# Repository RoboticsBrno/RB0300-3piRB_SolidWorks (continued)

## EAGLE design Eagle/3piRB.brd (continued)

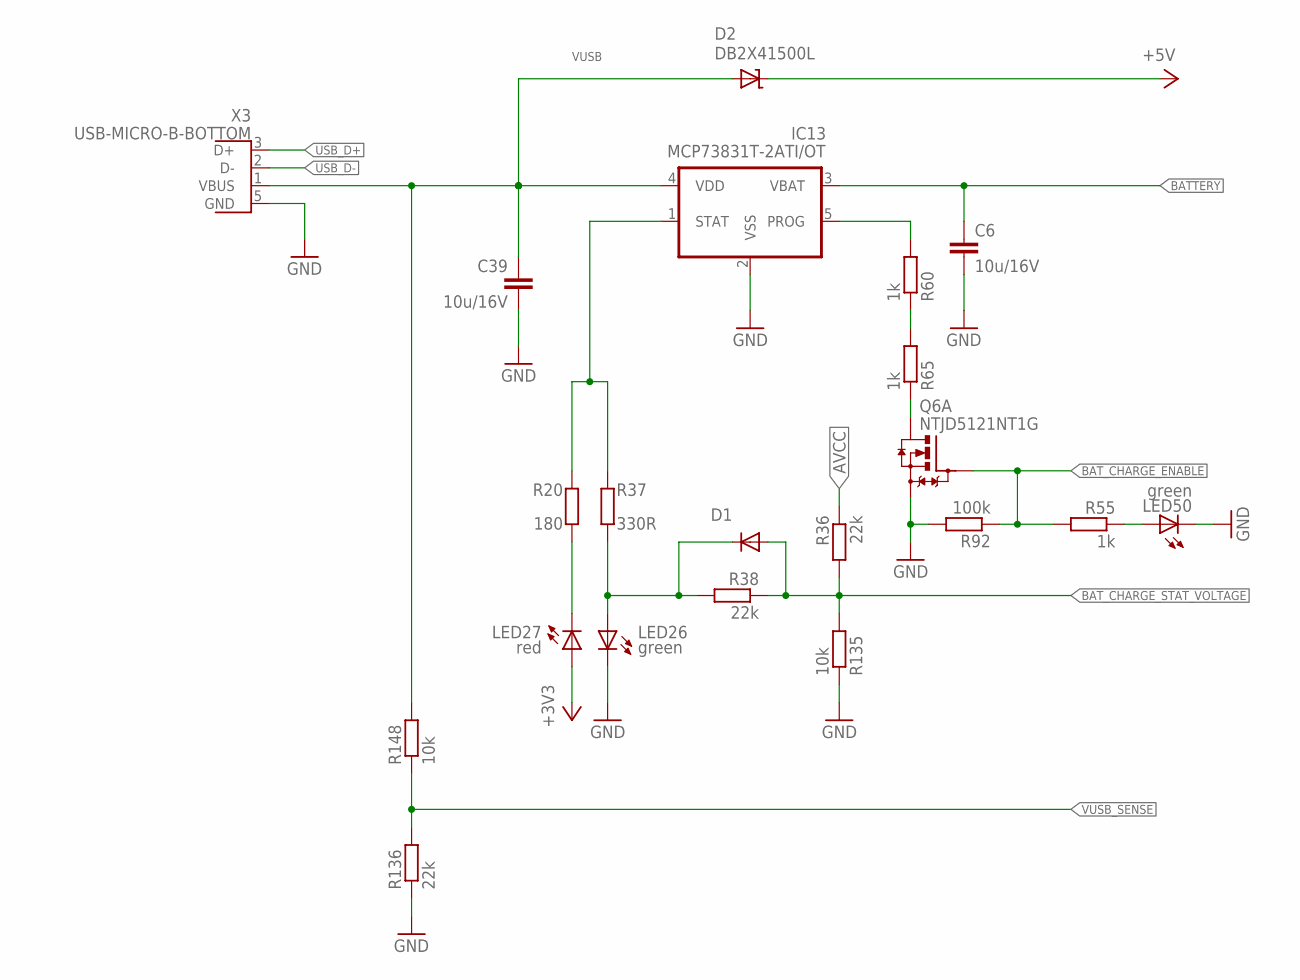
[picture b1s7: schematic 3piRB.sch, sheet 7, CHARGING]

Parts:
C6, C39: 10u/16V; C0805
D1: DIODE-0603; D0603
D2: DB2X41500L; SOD123
IC13: MCP73831T-2ATI/OT; SOT95P300X145-5N
LED26, LED50: green; CHIPLED_0603
LED27: red; CHIPLED_0603
Q6: NTJD5121NT1G; SOT363
R20: 180; _0402MP
R36, R38, R136: 22k; _0402MP
R37: 330R; _0402MP
R55, R60, R65: 1k; _0402MP
R92: 100k; _0402MP
R135, R148: 10k; _0402MP
X3: USB-MICRO-B-BOTTOM; USB-MICRO-B-BOTTOM-MOLEX

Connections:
+3V3: LED27.A; also elsewhere on the board
+5V: D2.C; also elsewhere on the board
AVCC: R36.1; also elsewhere on the board
BATTERY: C6.1, IC13.3 (VBAT); also elsewhere on the board
BAT_CHARGE_ENABLE: Q6.2 (G), R55.2, R92.1; also elsewhere on the board
BAT_CHARGE_STAT_VOLTAGE: D1.A, R36.2, R38.1, R135.2; also elsewhere on the board
GND: C6.2, C39.2, IC13.2 (VSS), LED26.C, LED50.C, Q6.1 (S), R92.2, R135.1, R136.1, X3.5 (GND); also elsewhere on the board
I_CHARGE_PROG-: IC13.5 (PROG), R60.2
LED_R_21: LED50.A, R55.1
unnamed: IC13.1 (STAT), R20.2, R37.2
unnamed: D1.C, LED26.A, R37.1, R38.2
unnamed: LED27.C, R20.1
unnamed: Q6.6 (D), R65.1
unnamed: R60.1, R65.2
USB_D+: X3.3 (D+); also elsewhere on the board
USB_D-: X3.2 (D-); also elsewhere on the board
VUSB: C39.1, D2.A, IC13.4 (VDD), R148.2, X3.1 (VBUS); also elsewhere on the board
VUSB_SENSE: R136.2, R148.1; also elsewhere on the board

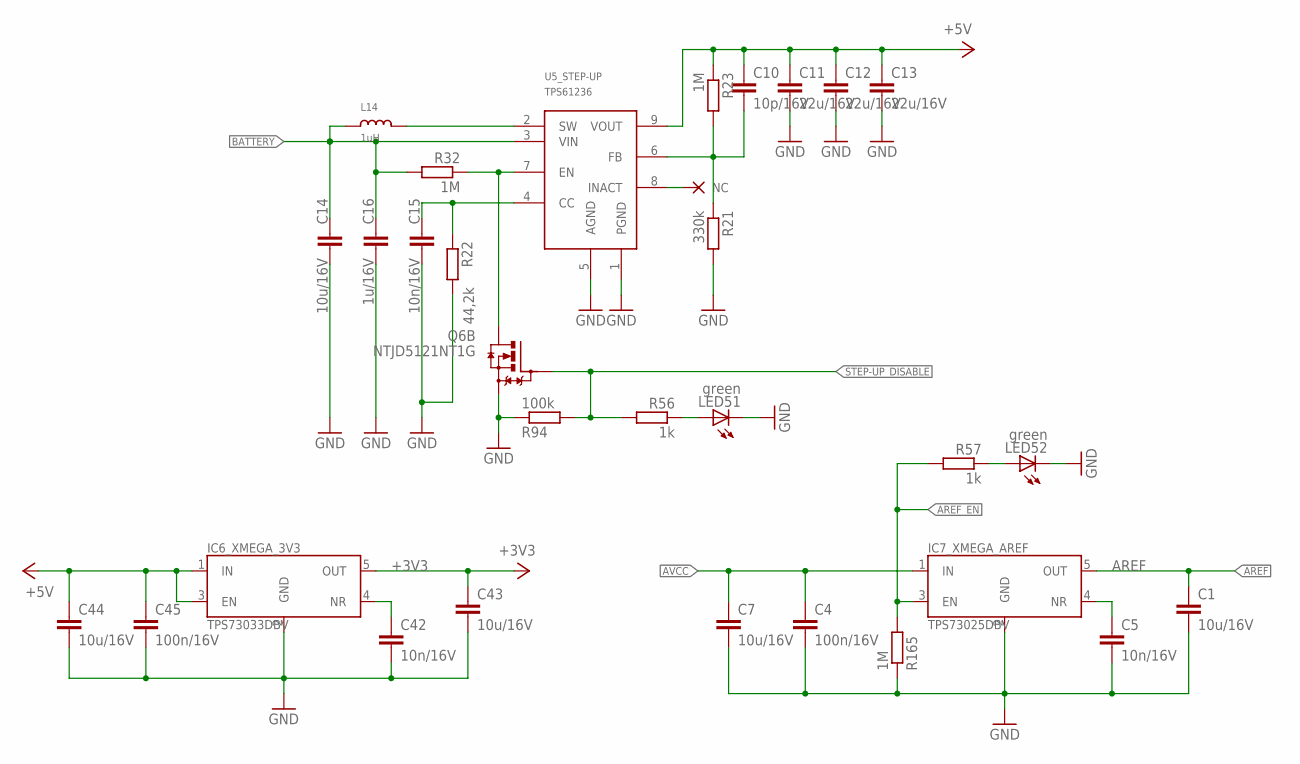
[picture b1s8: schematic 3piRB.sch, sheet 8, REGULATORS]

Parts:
C1, C7, C14, C43, C44: 10u/16V; C0805
C4, C45: 100n/16V; C0402
C5, C15, C42: 10n/16V; C0402
C10: 10p/16V; C0603
C11, C12, C13: 22u/16V; C0805; FARNELL 2611932
C16: 1u/16V; C0805
IC6_XMEGA_3V3: TPS73033DBV; SOT23-DBV
IC7_XMEGA_AREF: TPS73025DBV; SOT23-DBV
L14: 1uH; XAL7030
LED51, LED52: green; CHIPLED_0603
Q6: NTJD5121NT1G; SOT363
R21: 330k; _0402MP
R22: 44,2k; _0402MP
R23, R32, R165: 1M; _0402MP
R56, R57: 1k; _0402MP
R94: 100k; _0402MP
U5_STEP-UP: TPS61236; VQFN

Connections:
+3V3: C43.1, IC6_XMEGA_3V3.5 (OUT); also elsewhere on the board
+5V: C10.1, C11.1, C12.1, C13.1, C44.1, C45.1, IC6_XMEGA_3V3.1 (IN), IC6_XMEGA_3V3.3 (EN), R23.1, U5_STEP-UP.9 (VOUT); also elsewhere on the board
AREF: C1.1, IC7_XMEGA_AREF.5 (OUT); also elsewhere on the board
AREF_EN: IC7_XMEGA_AREF.3 (EN), R57.2, R165.2; also elsewhere on the board
AVCC: C4.1, C7.1, IC7_XMEGA_AREF.1 (IN); also elsewhere on the board
BATTERY: C14.1, C16.1, L14.1, R32.2, U5_STEP-UP.3 (VIN); also elsewhere on the board
GND: C1.2, C4.2, C5.2, C7.2, C11.2, C12.2, C13.2, C14.2, C15.2, C16.2, C42.2, C43.2, C44.2, C45.2, IC6_XMEGA_3V3.2 (GND), IC7_XMEGA_AREF.2 (GND), LED51.C, LED52.C, Q6.4 (S), R21.2, R22.2, R94.1, R165.1, U5_STEP-UP.1 (PGND), U5_STEP-UP.5 (AGND); also elsewhere on the board
LED_R_22: LED51.A, R56.1
LED_R_23: LED52.A, R57.1
NC_STEP-UP_INACT: U5_STEP-UP.8 (INACT)
STAB_2V5_NR: C5.1, IC7_XMEGA_AREF.4 (NR)
STAB_3V3_NR: C42.1, IC6_XMEGA_3V3.4 (NR)
STEP-UP_DISABLE: Q6.5 (G), R56.2, R94.2; also elsewhere on the board
STEP-UP_ENABLE: Q6.3 (D), R32.1, U5_STEP-UP.7 (EN)
STEP_UP_CC: C15.1, R22.1, U5_STEP-UP.4 (CC)
STEP_UP_FB: C10.2, R21.1, R23.2, U5_STEP-UP.6 (FB)
STEP_UP_SW: L14.2, U5_STEP-UP.2 (SW)

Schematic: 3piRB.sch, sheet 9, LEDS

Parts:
LED1, LED3, LED5, LED11, LED13, LED15, LED17, LED19: red; CHIPLED_0603
LED2, LED4, LED10, LED12, LED14, LED16, LED18, LED25, LED29, LED30, LED32, LED34, LED35, LED36, LED37, LED38, LED39, LED53: green; CHIPLED_0603
R5, R63, R139, R142, R143, R144, R145, R146, R147, R154: 1k; _0402MP
R100, R118, R120, R122, R124, R126, R128, R130: 150; _0402MP
R108, R119, R121, R123, R125, R127, R129, R131: 180; _0402MP

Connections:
3PI_VBAT: R63.2; also elsewhere on the board
3PI_VBST: R144.2; also elsewhere on the board
3PI_VCC_5V: R146.2; also elsewhere on the board
+3V3: LED1.A, LED3.A, LED5.A, LED11.A, LED13.A, LED15.A, LED17.A, LED19.A, R143.2; also elsewhere on the board
+5V: R139.2; also elsewhere on the board
AREF: R145.2; also elsewhere on the board
BATTERY: R154.2; also elsewhere on the board
BT_COM_VOLTAGE: R5.2; also elsewhere on the board
GND: LED2.C, LED4.C, LED10.C, LED12.C, LED14.C, LED16.C, LED18.C, LED25.C, LED29.C, LED30.C, LED32.C, LED34.C, LED35.C, LED36.C, LED37.C, LED38.C, LED39.C, LED53.C; also elsewhere on the board
IOREF: R147.2; also elsewhere on the board
LED_0: R100.2, R108.2; also elsewhere on the board
LED_1: R118.2, R119.2; also elsewhere on the board
LED_2: R120.2, R121.2; also elsewhere on the board
LED_3: R122.2, R123.2; also elsewhere on the board
LED_4: R124.2, R125.2; also elsewhere on the board
LED_5: R126.2, R127.2; also elsewhere on the board
LED_6: R128.2, R129.2; also elsewhere on the board
LED_7: R130.2, R131.2; also elsewhere on the board
LED_G_0: LED1.C, R108.1
LED_G_1: LED3.C, R119.1
LED_G_2: LED5.C, R121.1
LED_G_3: LED11.C, R123.1
LED_G_4: LED13.C, R125.1
LED_G_5: LED15.C, R127.1
LED_G_6: LED17.C, R129.1
LED_G_7: LED19.C, R131.1
LED_R_0: LED25.A, R100.1
LED_R_1: LED2.A, R118.1
LED_R_2: LED4.A, R120.1
LED_R_3: LED10.A, R122.1
LED_R_4: LED12.A, R124.1
LED_R_5: LED14.A, R126.1
LED_R_6: LED16.A, R128.1
LED_R_7: LED18.A, R130.1
LED_R_9: LED29.A, R5.1
LED_R_10: LED30.A, R154.1
LED_R_11: LED32.A, R139.1
LED_R_13: LED34.A, R142.1
LED_R_14: LED35.A, R143.1
LED_R_15: LED36.A, R144.1
LED_R_16: LED37.A, R145.1
LED_R_17: LED38.A, R146.1
LED_R_18: LED39.A, R147.1
LED_R_24: LED53.A, R63.1
VUSB: R142.2; also elsewhere on the board

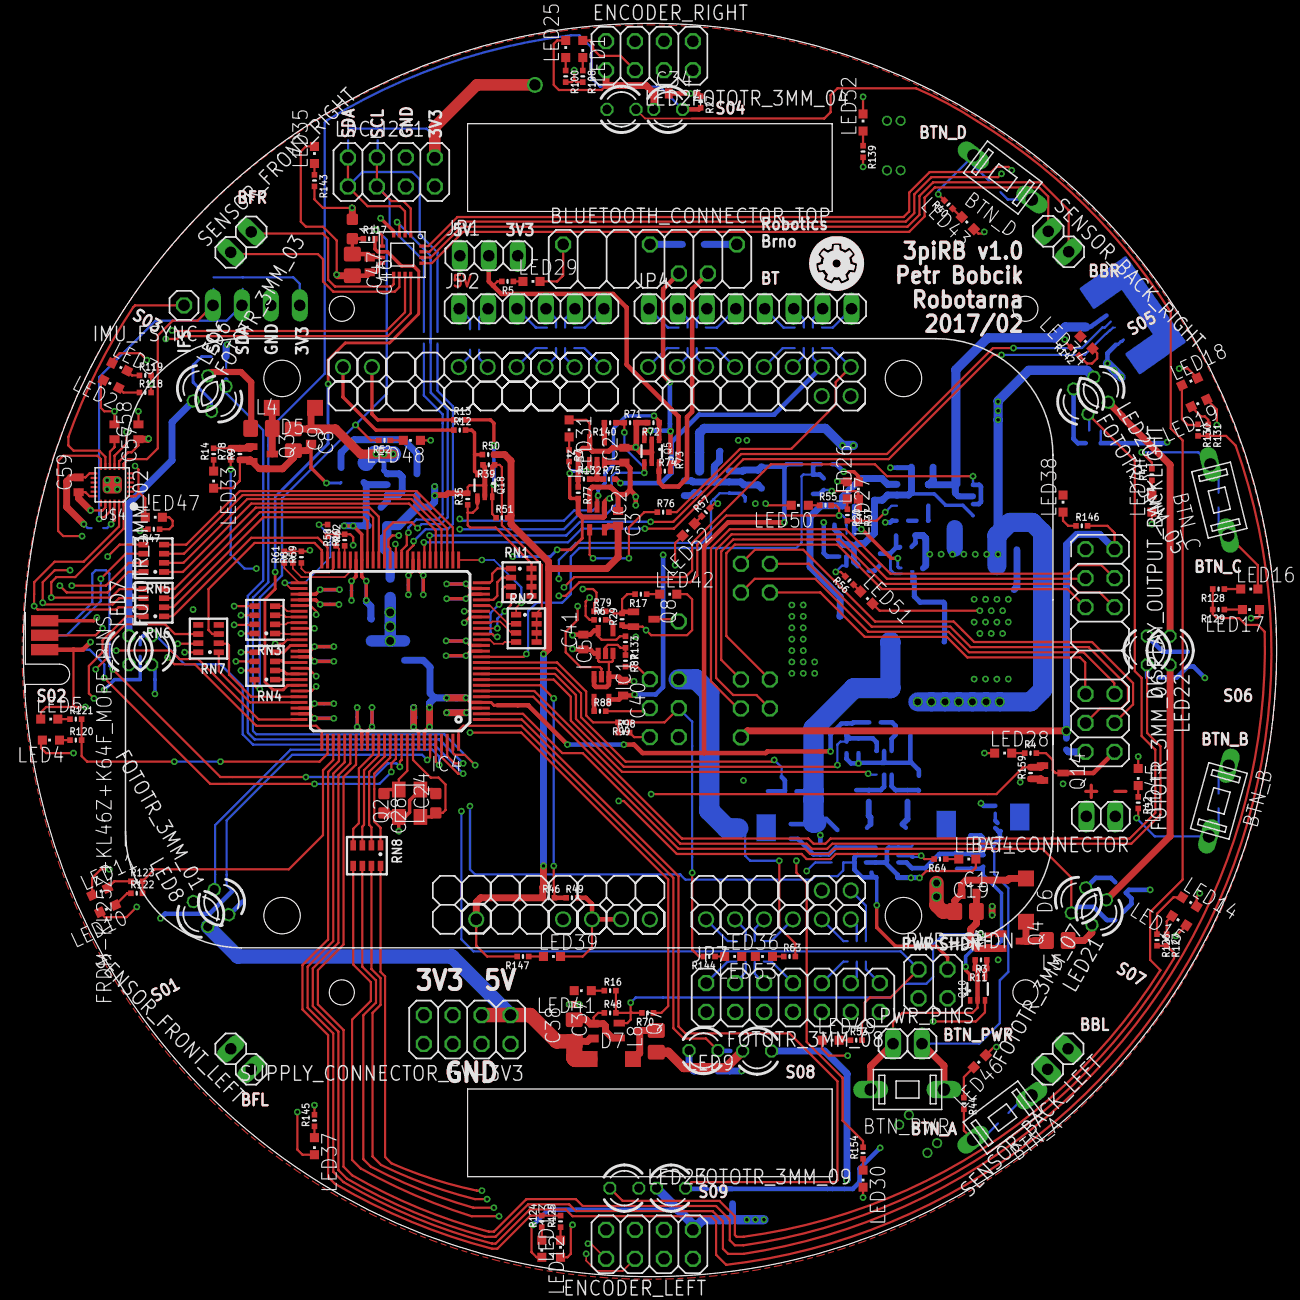
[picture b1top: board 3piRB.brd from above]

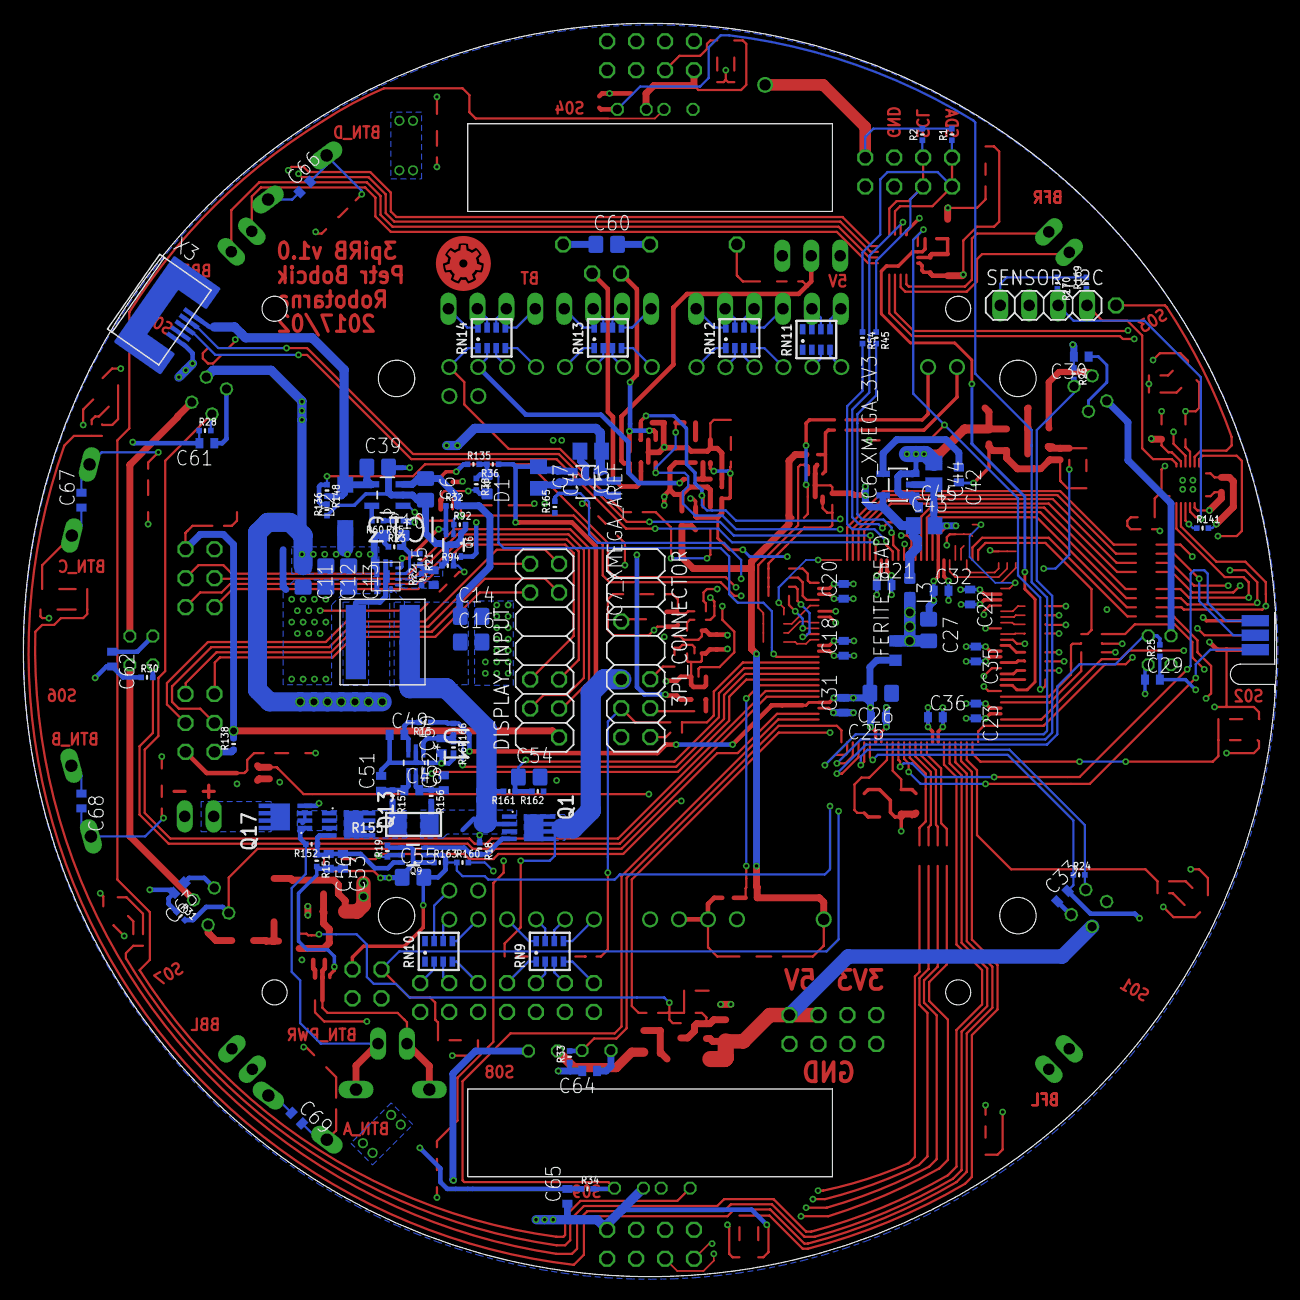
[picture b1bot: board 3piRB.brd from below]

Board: 4 copper layers, 110.0 x 110.0 mm, 341 parts (121 on the bottom side), 280 nets.

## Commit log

2018-09-04 Nahraná celá práce SOČ
2018-09-12 Update README.txt
    Rozšířené README
2018-09-12 Rename README.txt to README.md
2018-09-12 Update README.md
    Přidány obrázky, opravené překlepy
2018-09-12 Update README.md
    Zkouška odstavce u README
2018-09-12 Update README.md
    Opraveny odkazy na stránky a tučnost textu u README
2018-09-12 Update README.md
    Rozšířen text, přidán obrázek ze SolidoWorksu s rozloženým pohledem, opravena tučnost u seznamu u README
2018-09-12 Update README.md
    Opraven text u README
